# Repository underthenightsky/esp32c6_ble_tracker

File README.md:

# ESP32-C6 BLE Tracker — Low-Power / IMU-Gated Edition

Targets roughly **10 days on a 1000mAh battery** for an asset that
moves ~2 hrs/day, by only running BLE/WiFi when something's actually
happening — not on a fixed timer.

## Trade-off vs the other firmware variants

This version does **not** serve its own local web page. It's asleep
almost all the time, so it can't reliably answer HTTP requests — it
only pushes to your `ble_tracker_server`. If you want the
always-reachable local page, use `esp32_ble_tracker` (or
`particle_ble_tracker`) instead. You can't have both always-on local
browsability and this level of battery life on the same design — the
whole power saving comes from the radios being off almost all the
time.

## How it works

**Stationary** (the default state):
- Deep sleep, ~10 µA
- LIS3DH accelerometer armed for wake-on-motion, ~2-5 µA
- Nothing scans, nothing transmits — total draw ~15 µA
- Optional heartbeat (`HEARTBEAT_INTERVAL_S`, default 15 min): wakes
  briefly to re-push the last known position so your dashboard's
  "last seen" doesn't go stale for hours during a long stationary
  spell. Cheap since it's infrequent and skips the BLE scan entirely.

**Moving** (triggered by the IMU's motion interrupt):
- BLE scan burst (`SCAN_BURST_MS`, ~4-5s) → one-shot position estimate
- Moved ≥ `MOVE_THRESHOLD_M` (default 5m) since the last push? →
  connect WiFi, push to the server
- Didn't move that far? → skip WiFi entirely this cycle
- Re-checks every `ACTIVE_INTERVAL_S` (10s) using **light sleep**
  between cycles, which preserves the WiFi association — so a
  continuously-moving asset doesn't pay a full reconnect cost every
  10 seconds, just periodic scan+push bursts
- After `MAX_STATIONARY_CONFIRMS` (default 3, ~30s) consecutive
  checks with no real movement, drops WiFi and returns to deep,
  IMU-gated sleep

## Hardware

- ESP32-C6 dev board
- LIS3DH accelerometer breakout (I2C)
- Wiring:
  - LIS3DH SDA/SCL → ESP32-C6 I2C pins
  - LIS3DH INT1 → `IMU_INT_GPIO` in the `.ino` (default `GPIO_NUM_3`)
    — **this must be GPIO0–7**, the only pins in the C6's LP/RTC
    domain that can wake it from deep sleep. This is a hardware
    constraint of the chip, not something you can change in software.
  - LIS3DH VIN/GND → same 3.3V rail as the ESP32

No accelerometer library needed — `imu_lis3dh.h` is a small hand-
rolled I2C register driver (the LIS3DH's register map is simple and
well-documented, so this avoids pulling in a full library for what's
really about 8 register writes).

## Libraries

Just **NimBLE-Arduino** (h2zero, tested with 2.x). Everything else
(WiFi, HTTPClient, deep/light sleep) is core to the ESP32 Arduino
package — make sure you have a recent-enough `arduino-esp32` core
version with ESP32-C6 support.

## Configure

At the top of the `.ino`:

```cpp
const char* WIFI_SSID       = "YOUR_WIFI_SSID";
const char* WIFI_PASS       = "YOUR_WIFI_PASSWORD";
const char* SERVER_HOST     = "https://tracker.yourdomain.com";
const char* SERVER_API_KEY  = "changeme";      // matches server's BLE_TRACKER_API_KEY
const char* DEVICE_ID       = "esp32c6-01";    // unique per device
```

And in `imu_lis3dh.h`, `LIS3DH_ADDR` (0x18 or 0x19 depending on your
board's SA0 pin state) and `LIS3DH_MOTION_THRESHOLD` (how firm a nudge
is needed to trigger a wake — lower = more sensitive/more frequent
wakes, higher = fewer false wakes but might miss gentle movement).

## The 10-day estimate — read this before you commit to a battery

| Period | Current | Basis |
|---|---|---|
| Stationary (deep sleep + IMU armed) | ~15 µA | Published ESP32-C6 deep sleep (~10µA) + LIS3DH standby (~2-5µA) figures |
| Moving (BLE scan + WiFi, light-sleep between cycles) | ~40-50 mA avg | Estimated from published component figures — WiFi connected+modem-sleep, BLE scan burst duty-cycled over the 10s active interval |

At 2 hrs/day moving: **~85-100 mAh/day → ~10-11 days on 1000mAh**
(before real-world derating for regulator efficiency and battery
discharge curve, which typically costs another 10-15%).

**This is a directional estimate, not a bench measurement of your
specific board.** The biggest source of uncertainty is the "moving"
state average current — it depends heavily on your WiFi AP's DTIM
interval, signal strength, and exactly how well light-sleep preserves
the WiFi association on your specific core version. Before finalizing
a battery/enclosure:

1. Flash this firmware and measure actual current draw with a
   multimeter (in series with the battery) or a USB power profiler,
   in both states
2. Adjust `ACTIVE_INTERVAL_S`, `MAX_STATIONARY_CONFIRMS`,
   `HEARTBEAT_INTERVAL_S`, and `LIS3DH_MOTION_THRESHOLD` based on what
   you actually measure and how the trade-off between battery life
   and tracking responsiveness feels for your use case
3. Re-run the math with your measured numbers before ordering
   batteries for a fleet of these

## Tuning cheat sheet

| Constant | Effect of increasing it |
|---|---|
| `MOVE_THRESHOLD_M` | Fewer pushes, more battery life, coarser tracking |
| `ACTIVE_INTERVAL_S` | Fewer scan/push cycles while moving, more battery life, less responsive tracking |
| `MAX_STATIONARY_CONFIRMS` | Longer before dropping back to deep sleep after motion stops, more conservative about "really stopped" |
| `HEARTBEAT_INTERVAL_S` | Less frequent stationary check-ins, better battery life, staler "last seen" during long idle periods |
| `LIS3DH_MOTION_THRESHOLD` | Firmer nudge needed to wake, fewer false wakes, might miss gentle movement |

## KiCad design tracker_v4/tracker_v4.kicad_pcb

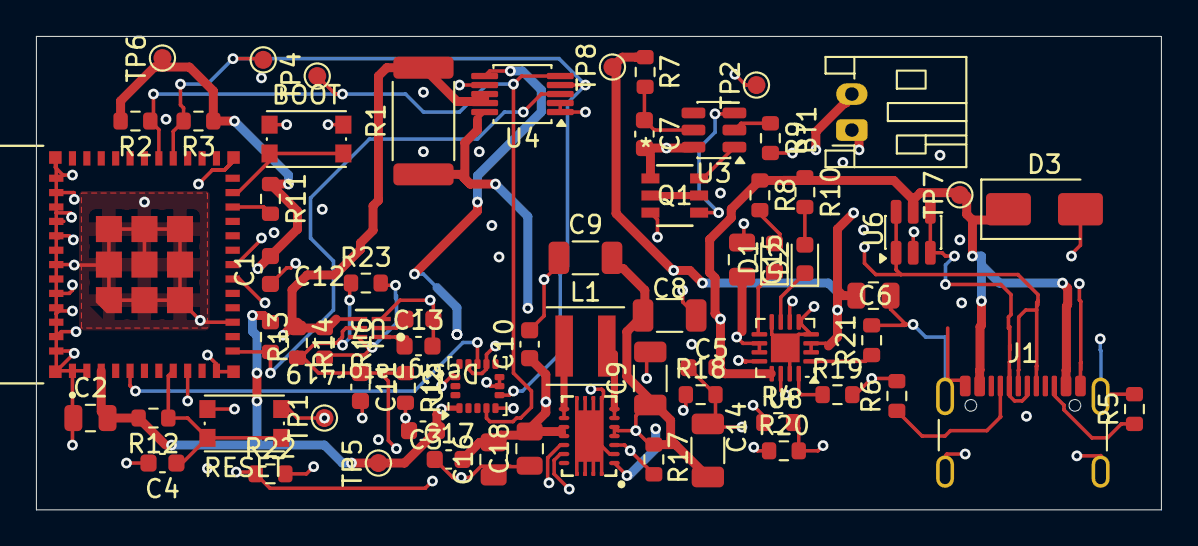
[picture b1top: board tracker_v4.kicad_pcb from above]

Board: 4 copper layers, 62.5 x 26.3 mm, 67 parts (0 on the bottom side), 39 nets.

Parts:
BOOT: SW_Push; SW_Push_1P1T_NO_CK_KMR2
BT1: Battery_Cell; JST_PH_S2B-PH-K_1x02_P2.00mm_Horizontal
C1, C3, C7, C10, C12, C13, C17: 100n; C_0603_1608Metric
C2, C6, C15, C16, C18: 10u; C_0805_2012Metric
C4: 1u; C_0603_1608Metric
C5: 4.7u; C_0603_1608Metric
C8, C9, C9#2, C14: 22u; C_1206_3216Metric
C11: 10n; C_0603_1608Metric
D1, D2: LED; LED_0603_1608Metric
D3: SMAJ5.0A; D_SMA
J1: USB_C_Receptacle_USB2.0_16P; USB_C_Receptacle_GCT_USB4105-xx-A_16P_TopMnt_Horizontal
L1: 1.5u; L_Coilcraft_XxL4020
Q1: DMG9926UDM-7; SOT-26_DIO
R1: 0.1; R_2512_6332Metric
R2, R3, R13: 4.7k; R_0603_1608Metric
R4, R9: 1.5k; R_0603_1608Metric
R5, R6: 5.1k; R_0603_1608Metric
R7: 499; R_0603_1608Metric
R8, R10: 680; R_0603_1608Metric
R11, R12, R21, R22: 10k; R_0603_1608Metric
R14: 1000k; R_0603_1608Metric
R15: 200k; R_0603_1608Metric
R16, R17: 1M; R_0603_1608Metric
R18: 180k; R_0603_1608Metric
R19: 2.1k; R_0603_1608Metric
R20: 47k; R_0603_1608Metric
R23: 10M; R_0603_1608Metric
RESET: SW_Push; SW_Push_1P1T_NO_CK_KMR2
TP1, TP2, TP3, TP4, TP5, TP6, TP7, TP8: TestPoint; TestPoint_Pad_D1.0mm
U1: ESP32-C6-MINI-1-N4; XCVR_ESP32-C6-MINI-1-N4
U2: LIS3DH; LGA-16_3x3mm_P0.5mm_LayoutBorder3x5y
U3: DW01A; SOT-23-6
U4: INA226AIDGSR; MSOP-10_3x3mm_P0.5mm
U5: TPS63020
U6: USBLC6-2SC6; SOT-23-6
U7: TPS3899DL01DSER; DSE0006A-IPC_A
U8: BQ24072RGT; VQFN-16-1EP_3x3mm_P0.5mm_EP1.6x1.6mm

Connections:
3v3: C1.2, C2.2, C3.1, C8.1, C9.1, C9#2.2, C14.2, R2.2, R3.1, R11.1, R12.2, R13.1, R17.1, TP5.1 (1_1), TP6.1 (1_1), U1.3 (3V3), U2.1 (VDD_IO), U2.7 (SDO), U2.8 (CS), U2.14 (VDD), U4.6 (VS+), U5.PIN4 (VOUT), U5.PIN5 (VOUT)
/Charging_and_Battery/BAT-: BT1.2 (-), C7.2, Q1.1, U3.6 (GND)
/Charging_and_Battery/PROTECT_MID: Q1.2, Q1.5
BAT+: BT1.1 (+), C6.2, R7.1, TP8.1 (1_1), U8.2 (BAT), U8.3 (BAT)
BUCK_EN: R16.2, R23.2, U5.PIN12 (EN), U7.6 (RESET_N)
BUCK_SYNC: R22.1, U1.9 (IO4), U5.PIN13 (SYNC)
GND: BOOT.1, C1.1, C2.1, C3.2, C4.2, C5.2, C6.1, C8.2, C9.2, C9#2.1, C10.2, C11.2, C12.2, C13.2, C14.1, C15.1, C16.1, C17.1, C18.1, D3.2 (A2), J1.A1 (GND), J1.A12 (GND), J1.B1 (GND), J1.B12 (GND), J1.SH (SHIELD), Q1.3, R4.2, R5.2, R6.2, R9.2, R15.2, R18.2, R19.2, R20.2, R21.2, R22.2, RESET.2, TP1.1 (1_1), TP2.1 (1_1), U1.1 (GND1), U1.2 (GND1), U1.11 (GND1), U1.14 (GND1), U1.36 (GND1), U1.37 (GND1), U1.38 (GND1), U1.39 (GND1), U1.40 (GND1), U1.41 (GND1), U1.42 (GND1), U1.43 (GND1), U1.44 (GND1), U1.45 (GND1), U1.46 (GND1), U1.47 (GND2), U1.48 (GND2), U1.49_1 (GND2), U1.49_2 (GND2), U1.49_3 (GND2), U1.49_4 (GND2), U1.49_5 (GND2), U1.49_6 (GND2), U1.49_7 (GND2), U1.49_8 (GND2), U1.49_9 (GND2), U1.50 (GND2), U1.51 (GND2), U1.52 (GND2), U1.53 (GND2), U2.5 (GND), U2.10 (GND), U2.12 (GND), U4.1 (A1), U4.2 (A0), U4.7 (GND), U5.PAD1 (PGND), U5.PAD2 (PGND), U5.PAD3 (PGND), U5.PAD4 (PGND), U5.PAD5 (PGND), U5.PAD6 (PGND), U5.PAD7 (PGND), U5.PAD8 (PGND), U5.PIN2 (GND), U6.2 (GND), U7.3 (GND), U8.4 (~CE), U8.5 (EN2), U8.8 (VSS), U8.15 (TD), U8.17 (VSS)
INA226_ALERT: R13.2, U1.12 (IO0), U4.3 (Alert)
LIS3DH_INT1: U1.5 (IO2), U2.11 (INT1)
unnamed: D1.2 (A), R8.2
unnamed: D1.1 (K), U8.9 (~CHG)
unnamed: D2.2 (A), R10.2
unnamed: D2.1 (K), U8.7 (~PGOOD)
unnamed: J1.A5 (CC1), R6.1
unnamed: J1.B5 (CC2), R5.1
unnamed: L1.1, U5.PIN8 (L1), U5.PIN9 (L1)
unnamed: L1.2, U5.PIN6 (L2), U5.PIN7 (L2)
unnamed: C4.1, R12.1, RESET.1, U1.8 (EN)
unnamed: R11.2, U1.22 (IO8)
unnamed: BOOT.2, U1.23 (IO9)
unnamed: R9.1, U3.2 (CS)
unnamed: Q1.4, U3.3 (OC)
unnamed: Q1.6, U3.1 (OD)
unnamed: C7.1, R7.2, U3.5 (VCC)
unnamed: R17.2, R18.1, U5.PIN3 (FB)
unnamed: C13.1, U7.1 (CTR)
unnamed: C12.1, U7.2 (CTS)
unnamed: R4.1, U8.12 (ILIM)
unnamed: R19.1, U8.16 (ISET)
unnamed: R20.1, U8.14 (TMR)
unnamed: R21.1, U8.1 (TS)
POWER_OUT: C15.2, R1.1, U4.10 (VIN+), U8.10 (OUT), U8.11 (OUT)
SCL: R2.1, TP4.1 (1_1), U1.29 (IO23), U2.4 (SPC), U4.5 (SCL)
SDA: R3.2, TP3.1 (1_1), U1.28 (IO22), U2.6 (SDI), U4.4 (SDA)
SHUNT_OUTPUT: C10.1, C16.2, C17.2, C18.2, R1.2, R14.1, R16.1, U4.8 (VBUS), U4.9 (VIN-), U5.PIN1 (VINA), U5.PIN10 (VIN), U5.PIN11 (VIN), U7.4 (VDD)
USB_DM: J1.A7 (D-), J1.B7 (D-), U1.17 (IO12), U6.3 (I/O2), U6.4 (I/O2)
USB_DP: J1.A6 (D+), J1.B6 (D+), U1.18 (IO13), U6.1 (I/O1), U6.6 (I/O1)
USB_VBUS: C5.1, D3.1 (A1), J1.A4 (VBUS), J1.A9 (VBUS), J1.B4 (VBUS), J1.B9 (VBUS), R8.1, R10.1, TP7.1 (1_1), U6.5 (VBUS), U8.6 (EN1), U8.13 (IN)
UVLO_SENSE: C11.1, R14.2, R15.1, R23.1, U7.5 (SENSE)

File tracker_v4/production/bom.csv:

Designator,Footprint,Quantity,Value,LCSC Part #
"BOOT, RESET",SW_Push_1P1T_NO_CK_KMR2,2,SW_Push,
BT1,JST_PH_S2B-PH-K_1x02_P2.00mm_Horizontal,1,Battery_Cell,
"C1, C10, C12, C13, C17, C3, C7",0603,7,100n,
C11,0603,1,10n,
"C14, C8, C9_2, C9",1206,4,22u,
"C15, C16, C18, C2, C6",0805,5,10u,
C4,0603,1,1u,
C5,0603,1,4.7u,
"D1, D2",0603,2,LED,
D3,D_SMA,1,SMAJ5.0A,
J1,USB_C_Receptacle_GCT_USB4105-xx-A_16P_TopMnt_Horizontal,1,USB_C_Receptacle_USB2.0_16P,
L1,L_Coilcraft_XxL4020,1,1.5u,
Q1,SOT-26_DIO,1,DMG9926UDM-7,
R1,2512,1,0.1,
"R10, R8",0603,2,680,
"R11, R12, R21, R22",0603,4,10k,
"R13, R2, R3",0603,3,4.7k,
R14,0603,1,1000k,
R15,0603,1,200k,
"R16, R17",0603,2,1M,
R18,0603,1,180k,
R19,0603,1,2.1k,
R20,0603,1,47k,
R23,0603,1,10M,
"R4, R9",0603,2,1.5k,
"R5, R6",0603,2,5.1k,
R7,0603,1,499,
"TP1, TP2, TP3, TP4, TP5, TP6, TP7, TP8",TestPoint_Pad_D1.0mm,8,TestPoint,
U1,XCVR_ESP32-C6-MINI-1-N4,1,ESP32-C6-MINI-1-N4,
U2,LGA-16_3x3mm_P0.5mm_LayoutBorder3x5y,1,LIS3DH,
U3,SOT-23-6,1,DW01A,
U4,MSOP-10_3x3mm_P0.5mm,1,INA226AIDGSR,C49851
U5,TPS63020,1,TPS63020,
U6,SOT-23-6,1,USBLC6-2SC6,
U7,DSE0006A-IPC_A,1,TPS3899DL01DSER,
U8,VQFN-16-1EP_3x3mm_P0.5mm_EP1.6x1.6mm,1,BQ24072RGT,
